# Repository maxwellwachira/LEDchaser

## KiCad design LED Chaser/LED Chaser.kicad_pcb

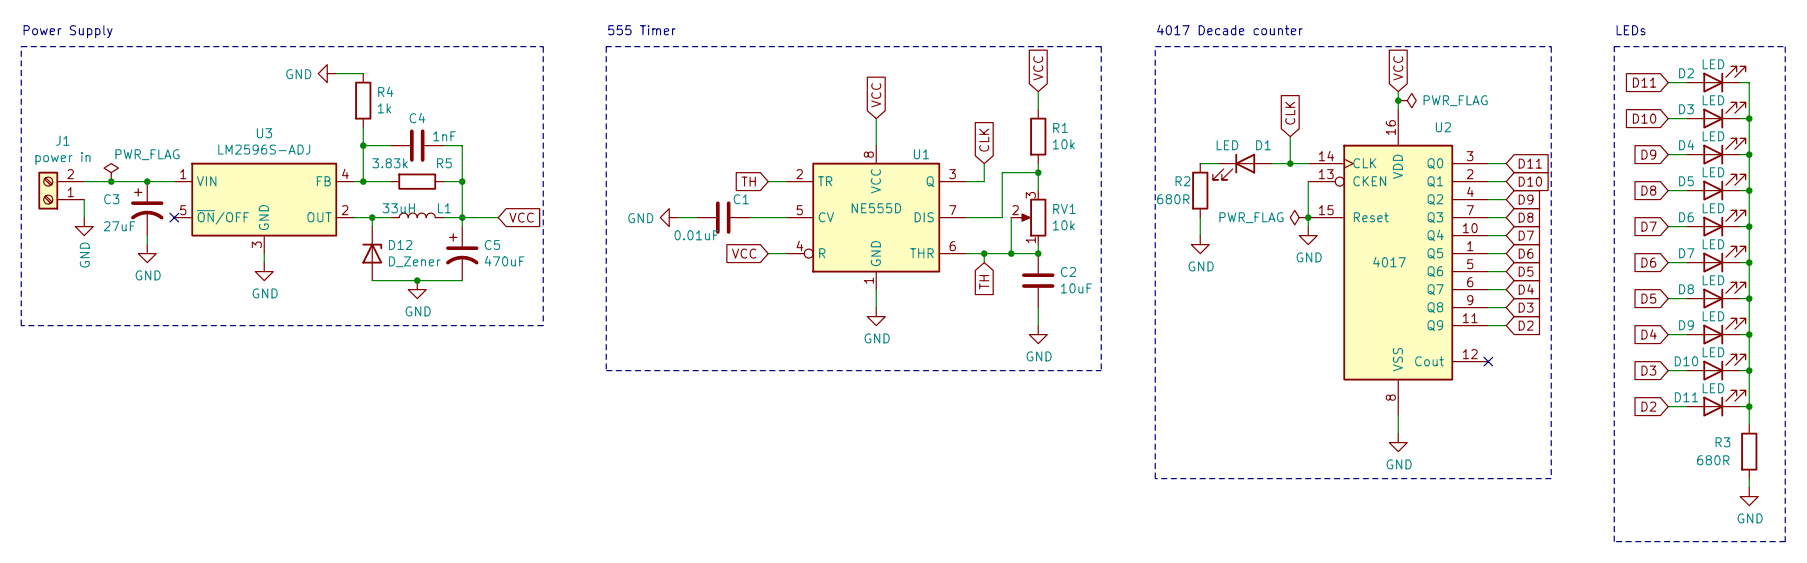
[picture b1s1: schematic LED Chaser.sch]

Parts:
C1: 0.01uF; C_0805_2012Metric
C2: 10uF; C_0805_2012Metric
C3: 27uF; CP_Elec_6.3x7.7
C4: 1nF; C_0805_2012Metric
C5: 470uF; CP_Elec_6.3x7.7
D1, D2, D3, D4, D5, D6, D7, D8, D9, D10, D11: LED; LED_D5.0mm
D12: D_Zener; D_0805_2012Metric
J1: power in; TerminalBlock_MetzConnect_Type073_RT02602HBLU_1x02_P5.08mm_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
L1: 33uH; L_Bourns_SRR1260
R1: 10k; R_0805_2012Metric
R2, R3: 680R; R_0805_2012Metric
R4: 1k; R_0805_2012Metric
R5: 3.83k; R_0805_2012Metric
RV1: 10k; Potentiometer_Bourns_3339P_Vertical
U1: NE555D; SOIC-8_3.9x4.9mm_P1.27mm
U2: 4017; DIP-16_W8.89mm_SMDSocket_LongPads
U3: LM2596S-ADJ; TO-263-5_TabPin3

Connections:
CLK: D1.2 (A), U1.3 (Q), U2.14 (CLK)
D2: D11.2 (A), U2.11 (Q9)
D3: D10.2 (A), U2.9 (Q8)
D4: D9.2 (A), U2.6 (Q7)
D5: D8.2 (A), U2.5 (Q6)
D6: D7.2 (A), U2.1 (Q5)
D7: D6.2 (A), U2.10 (Q4)
D8: D5.2 (A), U2.7 (Q3)
D9: D4.2 (A), U2.4 (Q2)
D10: D3.2 (A), U2.2 (Q1)
D11: D2.2 (A), U2.3 (Q0)
GND: C1.2, C2.2, C3.2, C5.2, D12.2 (A), J1.1, R2.2, R3.2, R4.1, U1.1 (GND), U2.8 (VSS), U2.13 (CKEN), U2.15 (Reset), U3.3 (GND)
unnamed: C1.1, U1.5 (CV)
unnamed: C3.1, J1.2, U3.1 (VIN)
unnamed: C4.2, R4.2, R5.2, U3.4 (FB)
unnamed: D1.1 (K), R2.1
unnamed: D2.1 (K), D3.1 (K), D4.1 (K), D5.1 (K), D6.1 (K), D7.1 (K), D8.1 (K), D9.1 (K), D10.1 (K), D11.1 (K), R3.1
unnamed: D12.1 (K), L1.1, U3.2 (OUT)
unnamed: R1.2, RV1.3, U1.7 (DIS)
TH: C2.1, RV1.1, RV1.2, U1.2 (TR), U1.6 (THR)
VCC: C4.1, C5.1, L1.2, R1.1, R5.1, U1.4 (R), U1.8 (VCC), U2.16 (VDD)

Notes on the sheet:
Power Supply
555 Timer
4017 Decade counter
LEDs

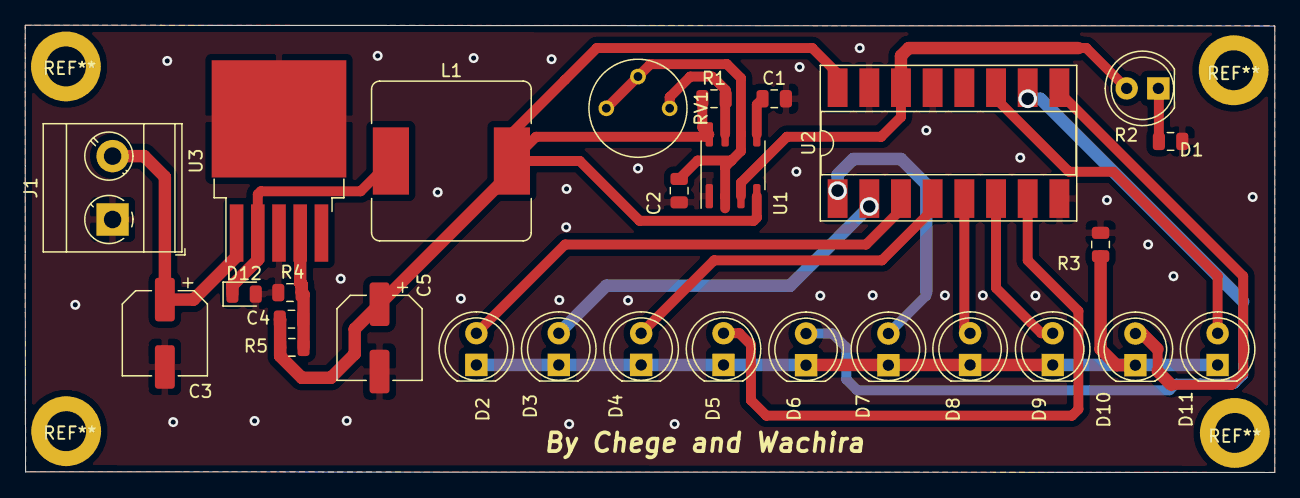
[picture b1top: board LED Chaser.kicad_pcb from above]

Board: 2 copper layers, 100.2 x 35.9 mm, 28 parts (0 on the bottom side), 21 nets.

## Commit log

2021-01-10 added power supply
2021-01-15 Added gitignore file
2021-01-15 Updated Report
